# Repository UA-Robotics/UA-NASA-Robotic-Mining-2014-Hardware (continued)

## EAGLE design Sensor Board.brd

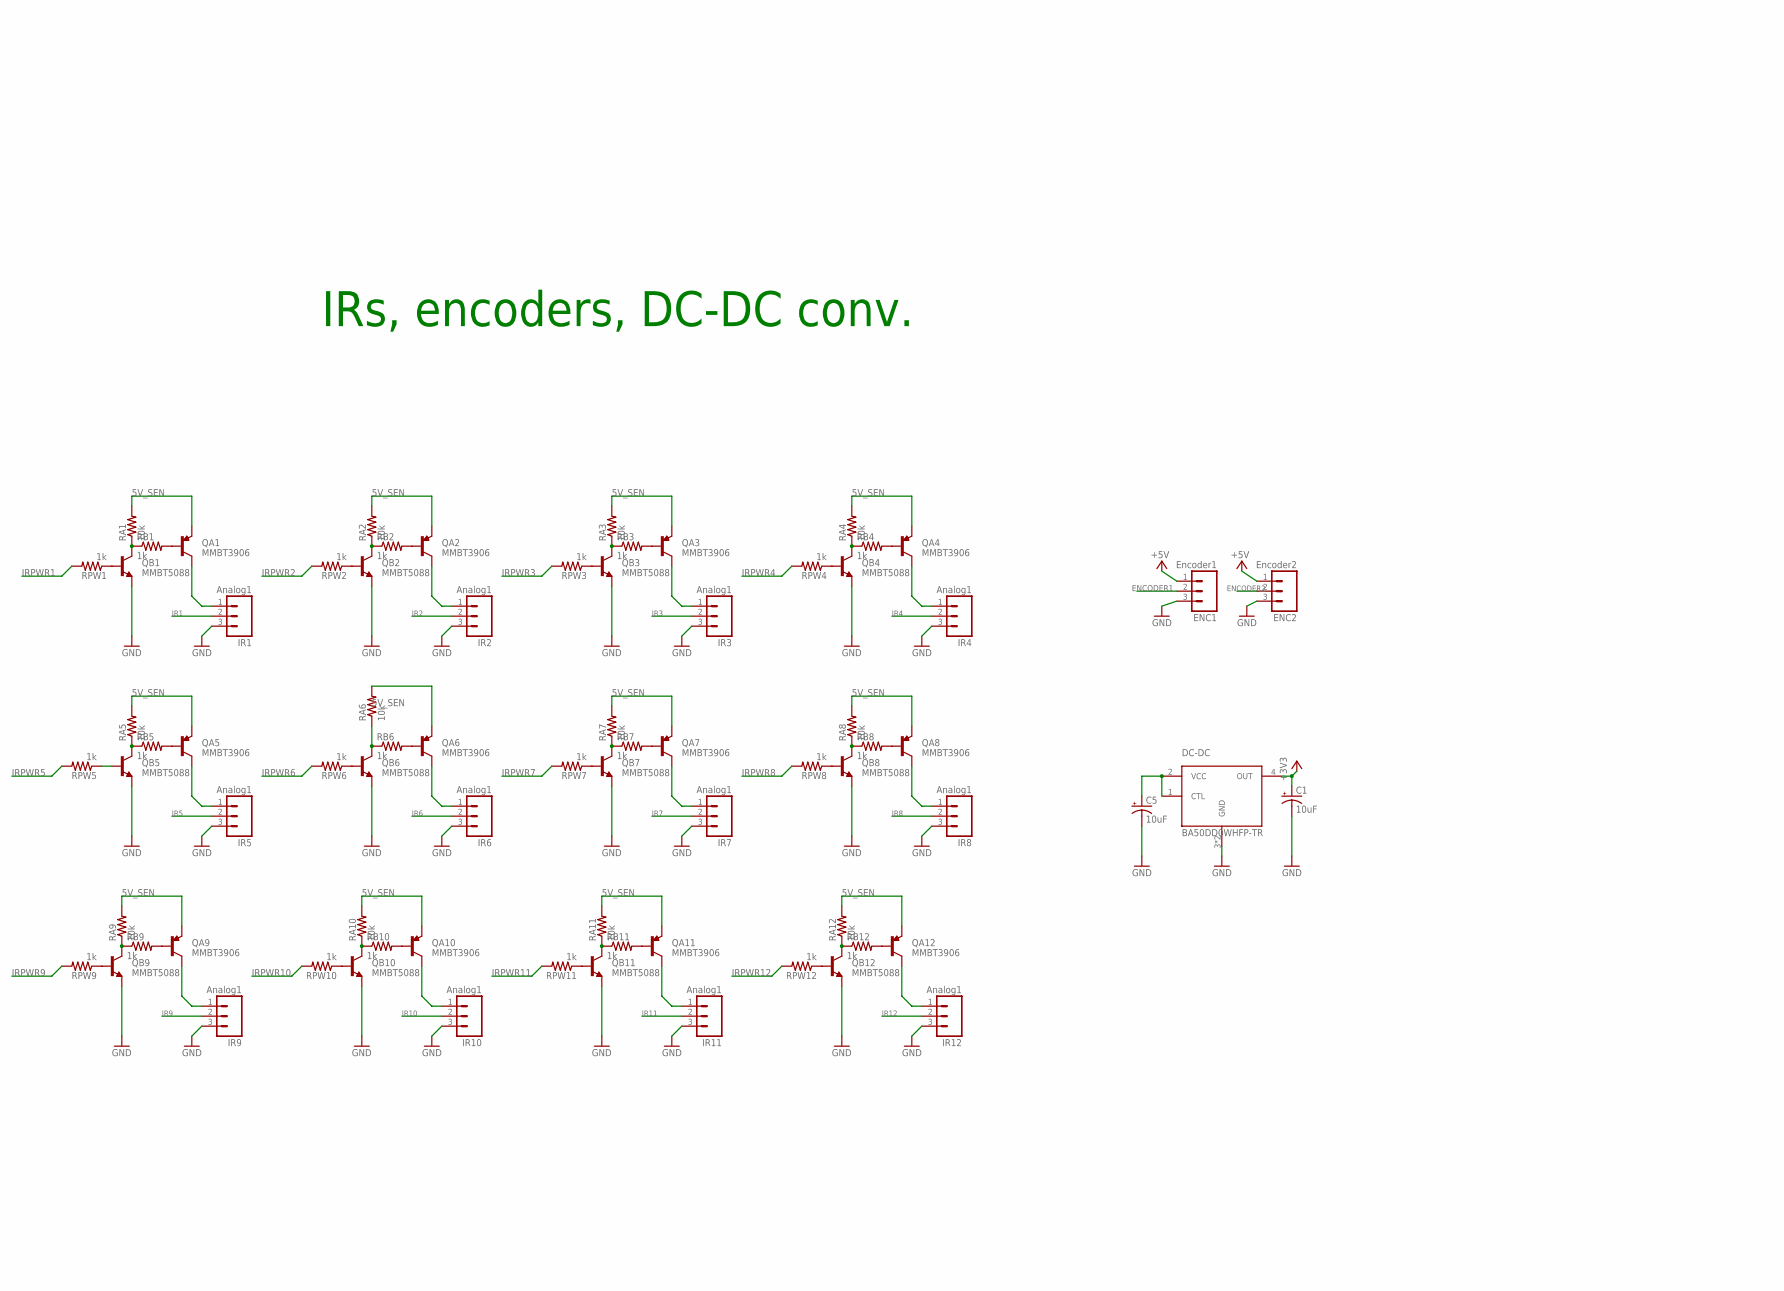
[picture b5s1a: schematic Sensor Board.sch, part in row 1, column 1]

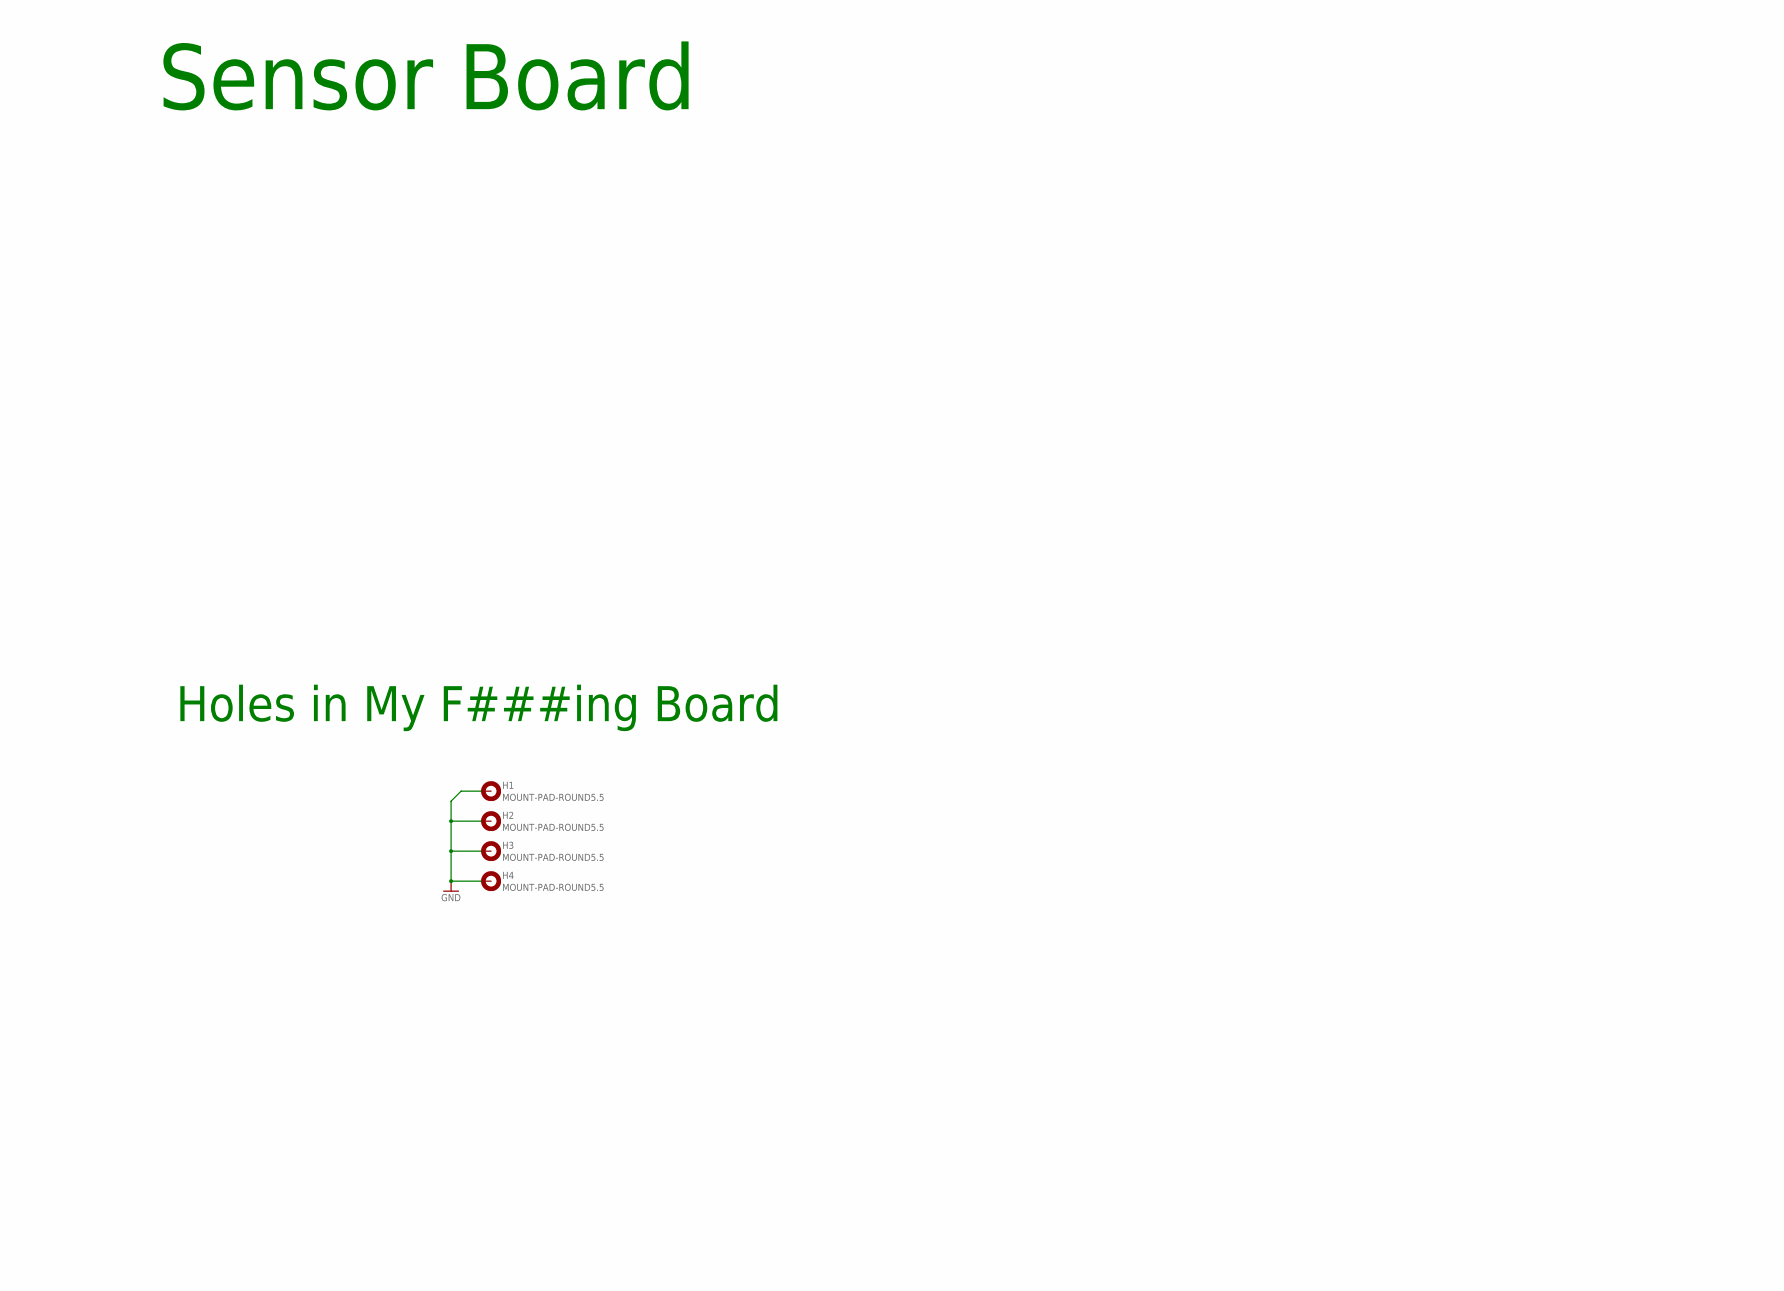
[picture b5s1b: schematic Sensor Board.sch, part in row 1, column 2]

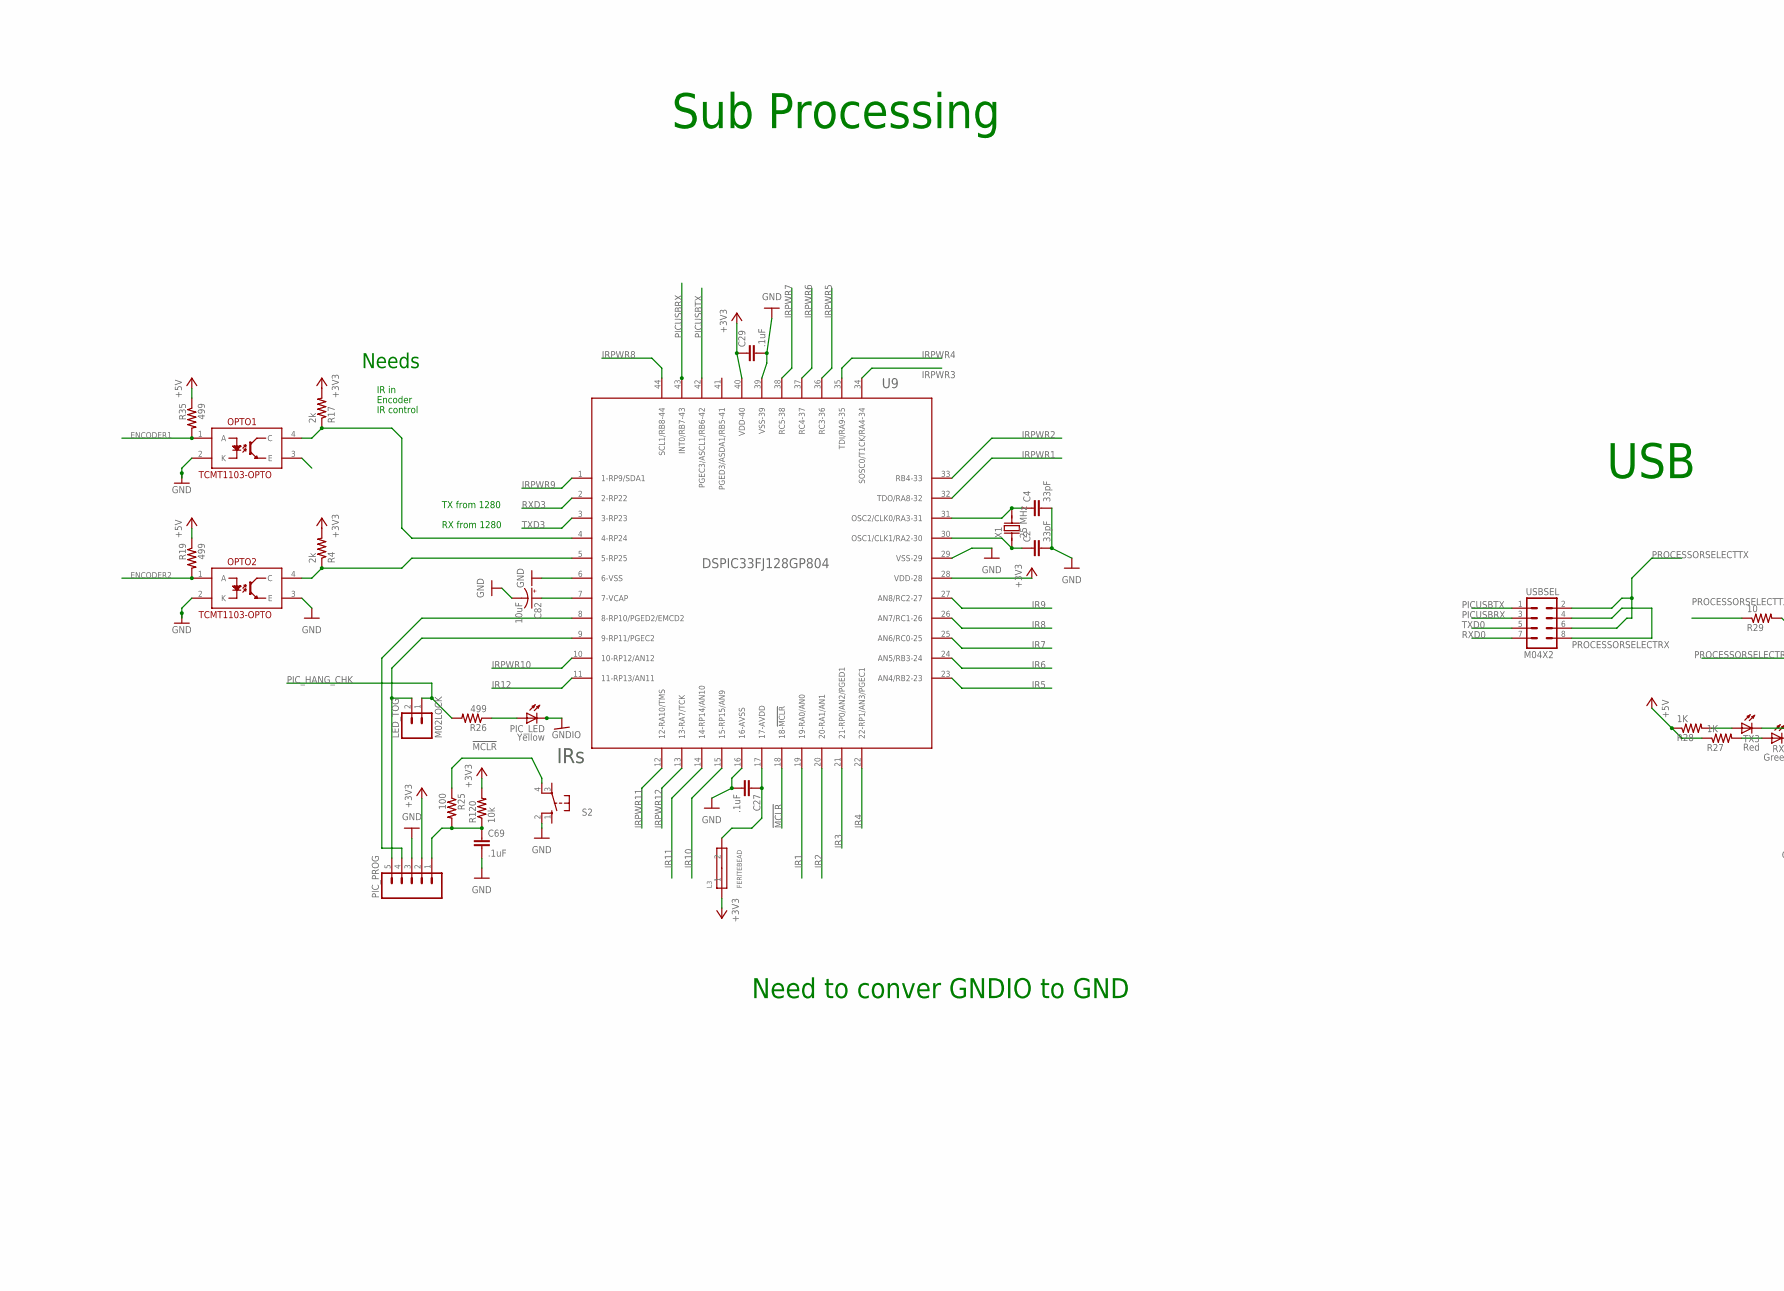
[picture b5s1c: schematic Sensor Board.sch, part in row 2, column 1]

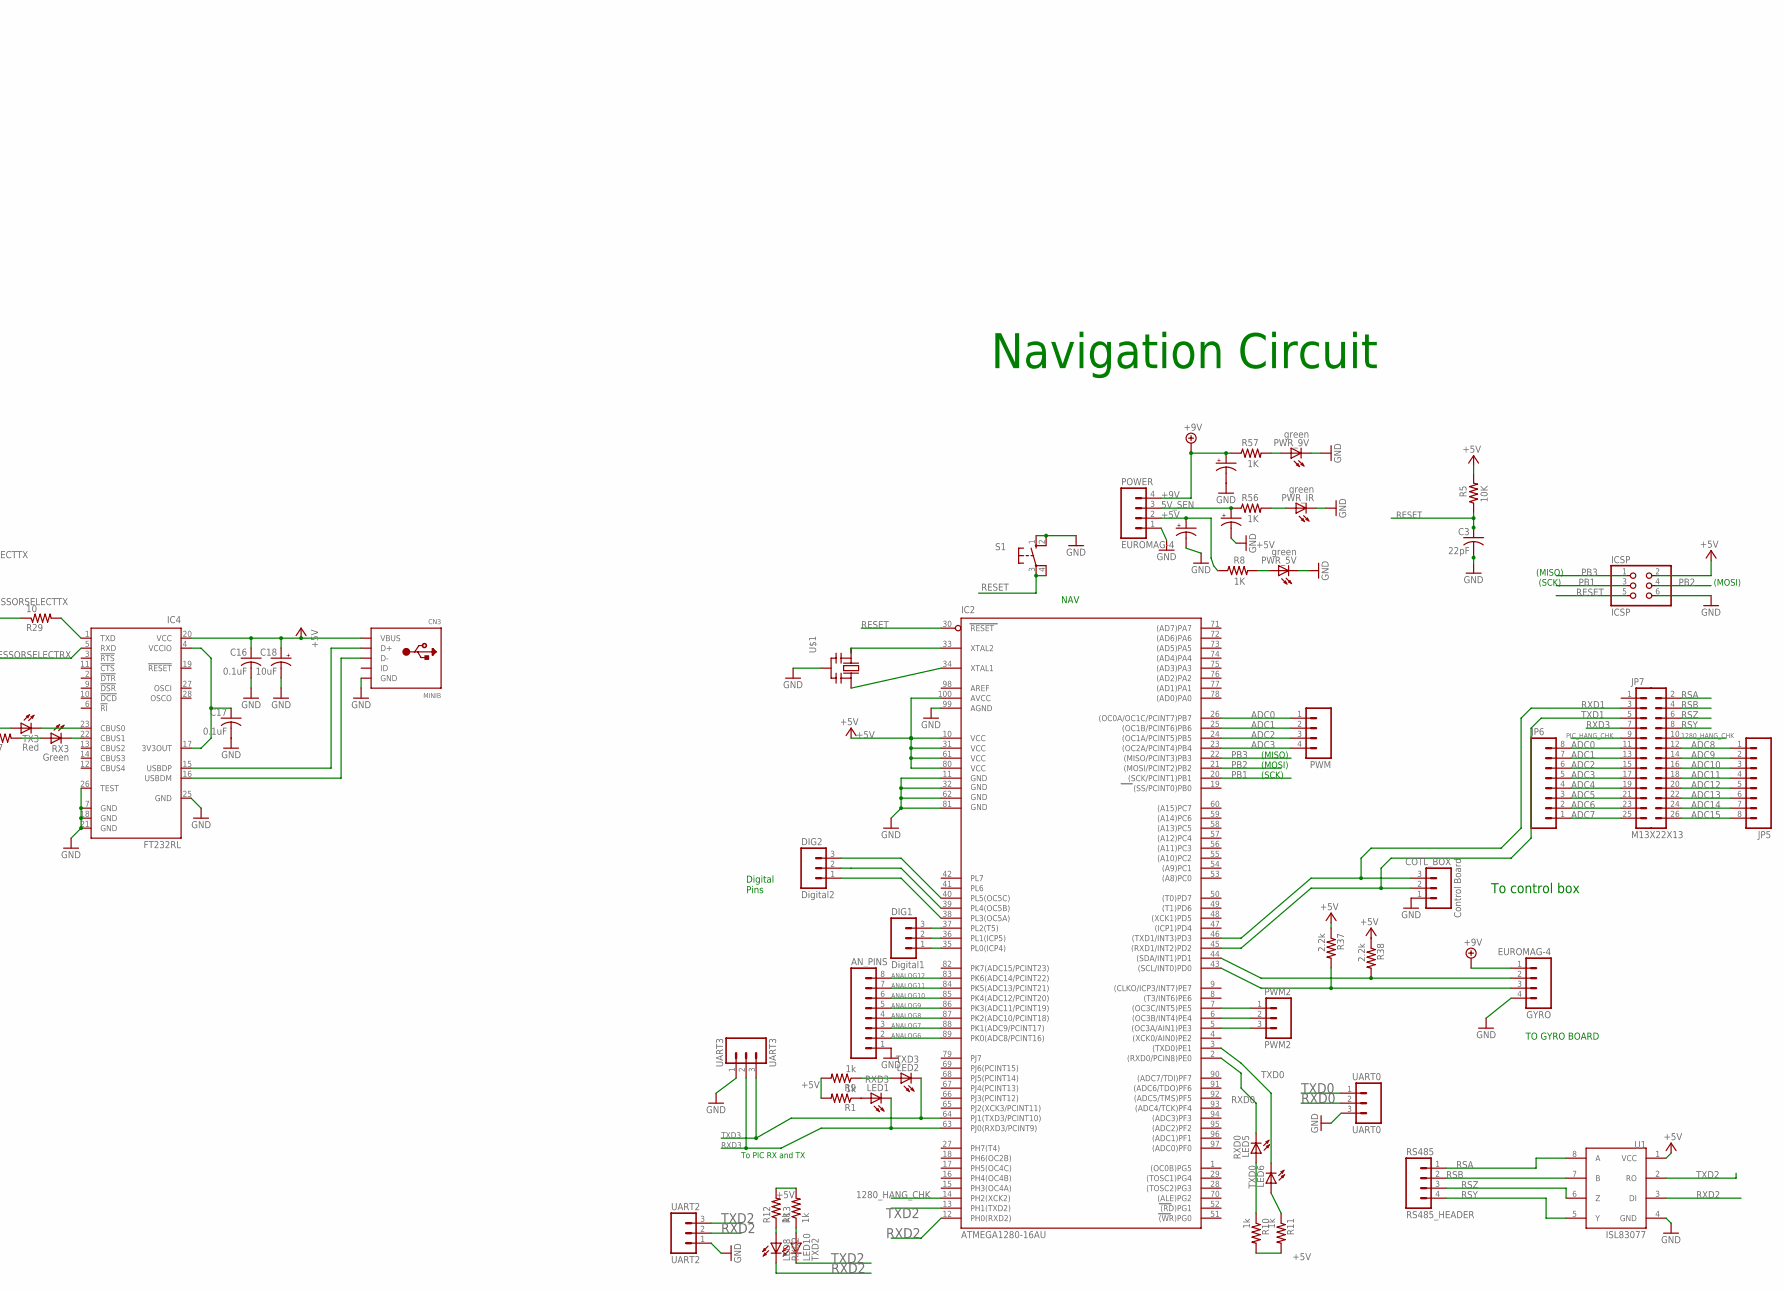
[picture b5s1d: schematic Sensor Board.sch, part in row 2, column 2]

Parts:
AN_PINS: M08LOCK_LONGPADS; 1X08_LOCK_LONGPADS
C1, C5: 10uF; EIA3216
C2, C4: 33pF; 0805
C3: 22pF; C0805K
C16, C17: 0.1uF; C0805K
C18: 10uF; EIA3528-KIT
C27, C29, C69: .1uF; 0805
C82: 10uF; POLC1206
CAN1, CAN2, CAN3: EMVY160ADA101MF55G; 140CLH-1010
CN3: MINIB; USB-MINIB
COTL_BOX: Control Board; MOLEX-1X3_LOCK
DC-DC: BA50DD0WHFP-TR; HRP5
DIG1: Digital1; M3
DIG2: Digital2; M3
ENC1: Encoder1; M3
ENC2: Encoder2; M3
GYRO: EUROMAG-4; M4
H1, H2, H3, H4: MOUNT-PAD-ROUND5.5; 5,5-PAD
IC2: ATMEGA1280-16AU; TQFP100
IC4: FT232RL; SSOP28
ICSP: ICSP; 2X03
IR1, IR2, IR3, IR4, IR5, IR6, IR7, IR8, IR9, IR10, IR11, IR12: Analog1; M3
JP5, JP6: M08LOCK_LONGPADS; 1X08_LOCK_LONGPADS
JP7: M13X22X13; 2X13
L3: FERITEBEAD; 0603
LED1: RXD3; CHIP-LED0805
LED2: TXD3; CHIP-LED0805
LED5: RXD0; CHIP-LED0805
LED6: TXD0; CHIP-LED0805
LED8: RXD2; CHIP-LED0805
LED10: TXD2; CHIP-LED0805
LED_TOG: M02LOCK; 1X02_LOCK
OPTO1, OPTO2: TCMT1103-OPTO; SSOP-4
PIC_LED: Yellow; CHIP-LED0805
PIC_PROG: M05LOCK_LONGPADS; 1X05_LOCK_LONGPADS
POWER: EUROMAG-4; M4
PWM: M04POLAR; MOLEX-1X4
PWM2: PWM2; MOLEX-1X3_LOCK
PWR_5V, PWR_9V: green; CHIPLED_0805
PWR_IR: green; CHIPLED_0805
QA1, QA2, QA3, QA4, QA5, QA6, QA7, QA8, QA9, QA10, QA11, QA12: MMBT3906; SOT23
QB1, QB2, QB3, QB4, QB5, QB6, QB7, QB8, QB9, QB10, QB11, QB12: MMBT5088; SOT23
R1, R9, R10, R11, R12, R13: 1k; R0805
R4, R17: 2k; R0805
R5: 10K; R0805
R8, R27, R28, R56, R57: 1K; R0805
R19, R26, R35: 499; R0805
R25: 100; R0805
R29: 10; R0805
R37, R38: 2.2k; R0805
R120: 10k; R0805
RA1, RA2, RA3, RA4, RA5, RA6, RA7, RA8, RA9, RA10, RA11, RA12: 10k; 0805
RB1, RB2, RB3, RB4, RB5, RB6, RB7, RB8, RB9, RB10, RB11, RB12: 1k; 0805
RPW1, RPW2, RPW3, RPW4, RPW5, RPW6, RPW7, RPW8, RPW9, RPW10, RPW11, RPW12: 1k; 0805
RS485_HEADER: RS485; M4-90
RX3: Green; CHIP-LED0805
S1, S2: 10-XX; B3F-10XX
TX3: Red; CHIP-LED0805
U1: ISL83077; SO08
U9: DSPIC33FJ128GP804; TQFP-44
U$1: CERMOSCILL-AWCSR; AWCSR
UART0: UART0; 1X03
UART2: UART2; 1X03
UART3: UART3; 1X03
USBSEL: M04X2; 2X4
X1: 25 MHz; XRCGB-CYL

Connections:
5V_SEN: CAN2.+, POWER.3, QA1.2 (E), QA2.2 (E), QA3.2 (E), QA4.2 (E), QA5.2 (E), QA6.2 (E), QA7.2 (E), QA8.2 (E), QA9.2 (E), QA10.2 (E), QA11.2 (E), QA12.2 (E), R56.1, RA1.2, RA2.2, RA3.2, RA4.2, RA5.2, RA6.2, RA7.2, RA8.2, RA9.2, RA10.2, RA11.2, RA12.2
1280_HANG_CHK: IC2.14 (PH2(XCK2)), JP7.10
!MCLR: R25.1, S2.4 (P1), U9.18 (18-!MCLR)
+3V3: C1.A (+), C29.1, DC-DC.4 (OUT), L3.1, PIC_PROG.2, R4.2, R17.2, R120.2, U9.28 (VDD-28), U9.40 (VDD-40)
+5V: C5.A (+), C16.1, C18.A (+), CAN3.+, CN3.VBUS, DC-DC.1 (CTL), DC-DC.2 (VCC), ENC1.1, ENC2.1, IC2.10 (VCC), IC2.31 (VCC1), IC2.61 (VCC2), IC2.80 (VCC3), IC2.100 (AVCC), IC4.20 (VCC), ICSP.2, POWER.2, R1.2, R5.2, R8.1, R9.2, R10.2, R11.2, R12.2, R13.2, R19.1, R27.1, R28.1, R35.1, R37.1, R38.1, U1.1 (VCC)
+9V: CAN1.+, GYRO.1, POWER.4, R57.1
ADC0: IC2.26 ((OC0A/OC1C/PCINT7)PB7), JP6.8, JP7.11, PWM.1
ADC1: IC2.25 ((OC1B/PCINT6)PB6), JP6.7, JP7.13, PWM.2
ADC2: IC2.24 ((OC1A/PCINT5)PB5), JP6.6, JP7.15, PWM.3
ADC3: IC2.23 ((OC2A/PCINT4)PB4), JP6.5, JP7.17, PWM.4
ADC4: JP6.4, JP7.19
ADC5: JP6.3, JP7.21
ADC6: JP6.2, JP7.23
ADC7: JP6.1, JP7.25
ADC8: JP5.1, JP7.12
ADC9: JP5.2, JP7.14
ADC10: JP5.3, JP7.16
ADC11: JP5.4, JP7.18
ADC12: JP5.5, JP7.20
ADC13: JP5.6, JP7.22
ADC14: JP5.7, JP7.24
ADC15: JP5.8, JP7.26
ANALOG6: AN_PINS.2, IC2.89 (PK0(ADC8/PCINT16))
ANALOG7: AN_PINS.3, IC2.88 (PK1(ADC9/PCINT17))
ANALOG8: AN_PINS.4, IC2.87 (PK2(ADC10/PCINT18))
ANALOG9: AN_PINS.5, IC2.86 (PK3(ADC11/PCINT19))
ANALOG10: AN_PINS.6, IC2.85 (PK4(ADC12/PCINT20))
ANALOG11: AN_PINS.7, IC2.84 (PK5(ADC13/PCINT21))
ANALOG12: AN_PINS.8, IC2.83 (PK6(ADC14/PCINT22))
ANBNKJDFBNDFKJL: OPTO1.4 (C), R17.1, U9.4 (4-RP24)
ANBNKJDFBNDFKJL1: OPTO2.4 (C), R4.1, U9.5 (5-RP25)
ENCODER1: ENC1.2, OPTO1.1 (A), R35.2
ENCODER2: ENC2.2, OPTO2.1 (A), R19.2
GND: AN_PINS.1, C1.C (-), C2.2, C3.2, C4.2, C5.C (-), C16.2, C17.2, C18.C (-), C27.2, C29.2, C69.2, C82.2 (-), CAN1.-, CAN2.-, CAN3.-, CN3.GND, COTL_BOX.1, DC-DC.3 (GND), DC-DC.G (GND), ENC1.3, ENC2.3, GYRO.4, H1.B5,5, H2.B5,5, H3.B5,5, H4.B5,5, IC2.11 (GND), IC2.32 (GND1), IC2.62 (GND2), IC2.81 (GND3), IC2.99 (AGND), IC4.7 (GND), IC4.18 (GND), IC4.21 (GND), IC4.25 (GND), IC4.26 (TEST), ICSP.6, IR1.3, IR2.3, IR3.3, IR4.3, IR5.3, IR6.3, IR7.3, IR8.3, IR9.3, IR10.3, IR11.3, IR12.3, OPTO1.2 (K), OPTO2.2 (K), OPTO2.3 (E), PIC_PROG.3, POWER.1, PWR_5V.C, PWR_9V.C, PWR_IR.C, QB1.2 (E), QB2.2 (E), QB3.2 (E), QB4.2 (E), QB5.2 (E), QB6.2 (E), QB7.2 (E), QB8.2 (E), QB9.2 (E), QB10.2 (E), QB11.2 (E), QB12.2 (E), S1.1 (S), S1.2 (S1), S2.2 (S1), U1.4 (GND), U9.6 (6-VSS), U9.16 (16-AVSS), U9.29 (VSS-29), U9.39 (VSS-39), U$1.2 (GND), UART0.3, UART2.1, UART3.1
GNDIO: PIC_LED.C
IR1: IR1.2, U9.19 (19-RA0/AN0)
IR2: IR2.2, U9.20 (20-RA1/AN1)
IR3: IR3.2, U9.21 (21-RP0/AN2/PGED1)
IR4: IR4.2, U9.22 (22-RP1/AN3/PGEC1)
IR5: IR5.2, U9.23 (AN4/RB2-23)
IR6: IR6.2, U9.24 (AN5/RB3-24)
IR7: IR7.2, U9.25 (AN6/RC0-25)
IR8: IR8.2, U9.26 (AN7/RC1-26)
IR9: IR9.2, U9.27 (AN8/RC2-27)
IR10: IR10.2, U9.15 (15-RP15/AN9)
IR11: IR11.2, U9.14 (14-RP14/AN10)
IR12: IR12.2, U9.11 (11-RP13/AN11)
IRPWR1: RPW1.2, U9.32 (TDO/RA8-32)
IRPWR2: RPW2.2, U9.33 (RB4-33)
IRPWR3: RPW3.2, U9.34 (SOSC0/T1CK/RA4-34)
IRPWR4: RPW4.2, U9.35 (TDI/RA9-35)
IRPWR5: RPW5.2, U9.36 (RC3-36)
IRPWR6: RPW6.2, U9.37 (RC4-37)
IRPWR7: RPW7.2, U9.38 (RC5-38)
IRPWR8: RPW8.2, U9.44 (SCL1/RB8-44)
IRPWR9: RPW9.2, U9.1 (1-RP9/SDA1)
IRPWR10: RPW10.2, U9.10 (10-RP12/AN12)
IRPWR11: RPW11.2, U9.12 (12-RA10/TMS)
IRPWR12: RPW12.2, U9.13 (13-RA7/TCK)
unnamed: QA2.1 (B), RB2.2
unnamed: QB2.3 (C), RA2.1, RB2.1
unnamed: PWR_5V.A, R8.2
unnamed: QB2.1 (B), RPW2.1
unnamed: QA1.1 (B), RB1.2
unnamed: IC2.34 (XTAL1), U$1.3 (OUT)
unnamed: IC2.33 (XTAL2), U$1.1 (IN)
unnamed: QB1.3 (C), RA1.1, RB1.1
unnamed: QB1.1 (B), RPW1.1
unnamed: IR1.1, QA1.3 (C)
unnamed: PIC_PROG.4, U9.8 (8-RP10/PGED2/EMCD2)
unnamed: LED2.A, R9.1
unnamed: C4.1, U9.31 (OSC2/CLK0/RA3-31), X1.3 (OUT)
unnamed: C2.1, U9.30 (OSC1/CLK1/RA2-30), X1.1 (IN)
unnamed: C69.1, PIC_PROG.1, R25.2, R120.1
unnamed: C82.1 (+), U9.7 (7-VCAP)
unnamed: IR2.1, QA2.3 (C)
unnamed: QA3.1 (B), RB3.2
unnamed: QB3.3 (C), RA3.1, RB3.1
unnamed: LED_TOG.2, PIC_PROG.5, U9.9 (9-RP11/PGEC2)
unnamed: QB3.1 (B), RPW3.1
unnamed: IC2.7 ((OC3C/INT5)PE5), PWM2.1
unnamed: C27.1, L3.2, U9.17 (17-AVDD)
unnamed: IR3.1, QA3.3 (C)
unnamed: QA4.1 (B), RB4.2
unnamed: QB4.3 (C), RA4.1, RB4.1
unnamed: QB4.1 (B), RPW4.1
unnamed: IR4.1, QA4.3 (C)
unnamed: QA5.1 (B), RB5.2
unnamed: IC2.6 ((OC3B/INT4)PE4), PWM2.2
unnamed: LED1.A, R1.1
unnamed: IC2.5 ((OC3A/AIN1)PE3), PWM2.3
unnamed: QB5.3 (C), RA5.1, RB5.1
unnamed: QB5.1 (B), RPW5.1
unnamed: LED10.A, R13.1
unnamed: IR5.1, QA5.3 (C)
unnamed: PWR_IR.A, R56.2
unnamed: LED8.A, R12.1
unnamed: PWR_9V.A, R57.2
unnamed: DIG1.1, IC2.35 (PL0(ICP4))
unnamed: LED6.A, R11.1
unnamed: DIG1.2, IC2.36 (PL1(ICP5))
unnamed: QA6.1 (B), RB6.2
unnamed: DIG1.3, IC2.37 (PL2(T5))
unnamed: DIG2.1, IC2.38 (PL3(OC5A))
unnamed: QB6.3 (C), RA6.1, RB6.1
unnamed: DIG2.2, IC2.39 (PL4(OC5B))
unnamed: DIG2.3, IC2.40 (PL5(OC5C))
unnamed: LED5.A, R10.1
unnamed: QB6.1 (B), RPW6.1
unnamed: IR6.1, QA6.3 (C)
unnamed: QA7.1 (B), RB7.2
unnamed: QB7.3 (C), RA7.1, RB7.1
unnamed: QB7.1 (B), RPW7.1
unnamed: GYRO.2, IC2.44 ((SDA/INT1)PD1), R38.2
unnamed: GYRO.3, IC2.43 ((SCL/INT0)PD0), R37.2
unnamed: IR7.1, QA7.3 (C)
unnamed: QA8.1 (B), RB8.2
unnamed: QB8.3 (C), RA8.1, RB8.1
unnamed: QB8.1 (B), RPW8.1
unnamed: IR8.1, QA8.3 (C)
unnamed: QA9.1 (B), RB9.2
unnamed: QB9.3 (C), RA9.1, RB9.1
unnamed: QB9.1 (B), RPW9.1
unnamed: IR9.1, QA9.3 (C)
unnamed: QA10.1 (B), RB10.2
unnamed: QB10.3 (C), RA10.1, RB10.1
unnamed: QB10.1 (B), RPW10.1
unnamed: CN3.D+, IC4.15 (USBDP)
unnamed: CN3.D-, IC4.16 (USBDM)
unnamed: IC4.23 (CBUS0), TX3.C
unnamed: IC4.22 (CBUS1), RX3.C
unnamed: R27.2, RX3.A
unnamed: R28.2, TX3.A
unnamed: IC4.1 (TXD), R29.2
unnamed: C17.1, IC4.4 (VCCIO), IC4.17 (3V3OUT)
unnamed: IR10.1, QA10.3 (C)
unnamed: QA11.1 (B), RB11.2
unnamed: QB11.3 (C), RA11.1, RB11.1
unnamed: QB11.1 (B), RPW11.1
unnamed: IR11.1, QA11.3 (C)
unnamed: QA12.1 (B), RB12.2
unnamed: QB12.3 (C), RA12.1, RB12.1
unnamed: QB12.1 (B), RPW12.1
unnamed: IR12.1, QA12.3 (C)
unnamed: PIC_LED.A, R26.1
PB1: IC2.20 ((SCK/PCINT1)PB1), ICSP.3
PB2: IC2.21 ((MOSI/PCINT2)PB2), ICSP.4
PB3: IC2.22 ((MISO/PCINT3)PB3), ICSP.1
PICUSBRX: U9.43 (INT0/RB7-43), USBSEL.3
PICUSBTX: U9.42 (PGEC3/ASCL1/RB6-42), USBSEL.1
PIC_HANG_CHK: JP7.9, LED_TOG.1, R26.2
PROCESSORSELECTRX: IC4.5 (RXD), USBSEL.4, USBSEL.8
PROCESSORSELECTTX: R29.1, USBSEL.2, USBSEL.6
RESET: C3.1, IC2.30 (RESET), ICSP.5, R5.1, S1.3, S1.4 (P1)
RSA: JP7.2, RS485_HEADER.1, U1.8 (A)
RSB: JP7.4, RS485_HEADER.2, U1.7 (B)
RSY: JP7.8, RS485_HEADER.4, U1.5 (Y)
RSZ: JP7.6, RS485_HEADER.3, U1.6 (Z)
RXD0: IC2.2 ((RXD0/PCIN8)PE0), LED5.C, UART0.2, USBSEL.7
RXD1: COTL_BOX.3, IC2.46 ((TXD1/INT3)PD3), JP7.3
RXD2: IC2.12 (PH0(RXD2)), LED8.C, U1.3 (DI), UART2.2
RXD3: IC2.63 (PJ0(RXD3/PCINT9)), JP7.7, LED1.C, U9.2 (2-RP22), UART3.2
TXD0: IC2.3 ((TXD0)PE1), LED6.C, UART0.1, USBSEL.5
TXD1: COTL_BOX.2, IC2.45 ((RXD1/INT2)PD2), JP7.5
TXD2: IC2.13 (PH1(TXD2)), LED10.C, U1.2 (RO), UART2.3
TXD3: IC2.64 (PJ1(TXD3/PCINT10)), LED2.C, U9.3 (3-RP23), UART3.3

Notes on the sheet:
(SCK)
(MISO)
(MOSI)
Sensor Board
Digital Pins
Sub Processing
NAV
IR in
Encoder
IR control
To control box
IRs
USB
Navigation Circuit
Holes in My F###ing Board
To PIC RX and TX
Needs
TO GYRO BOARD
IRs, encoders, DC-DC conv.
Need to conver GNDIO to GND
TX from 1280
RX from 1280

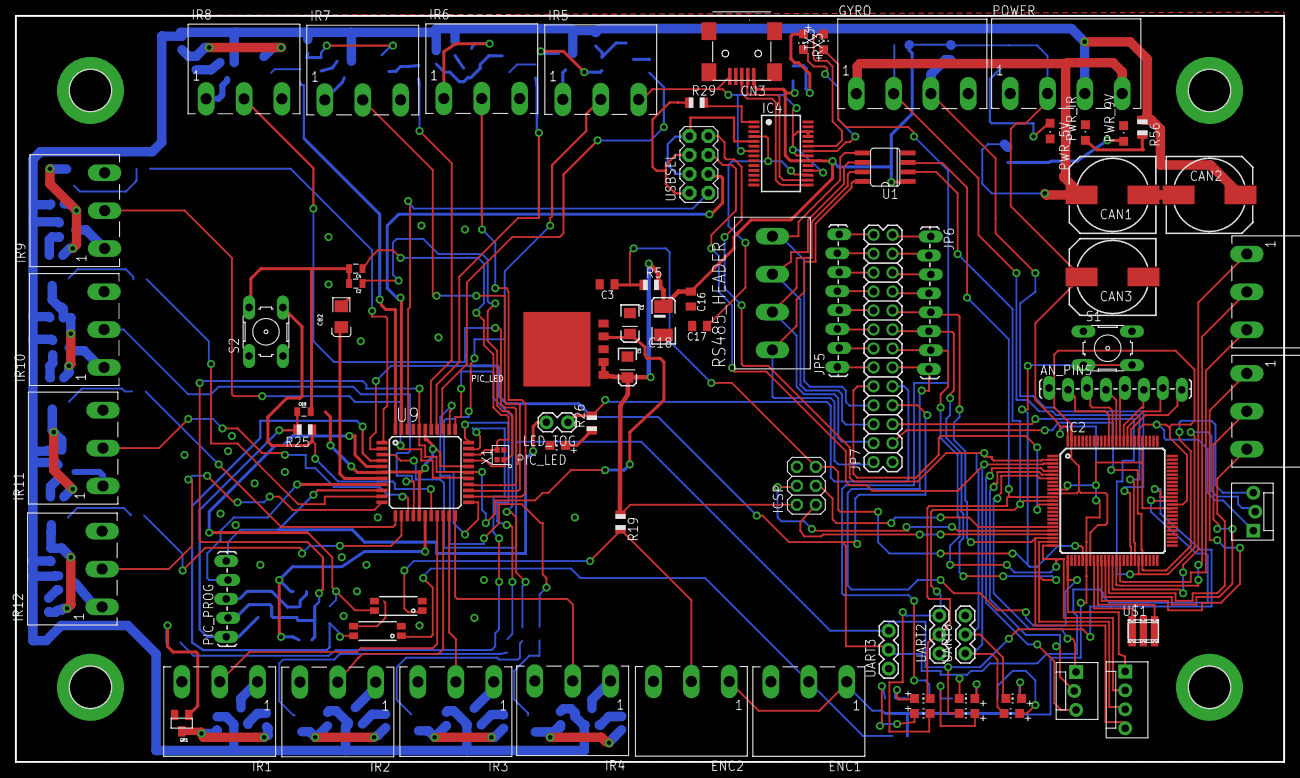
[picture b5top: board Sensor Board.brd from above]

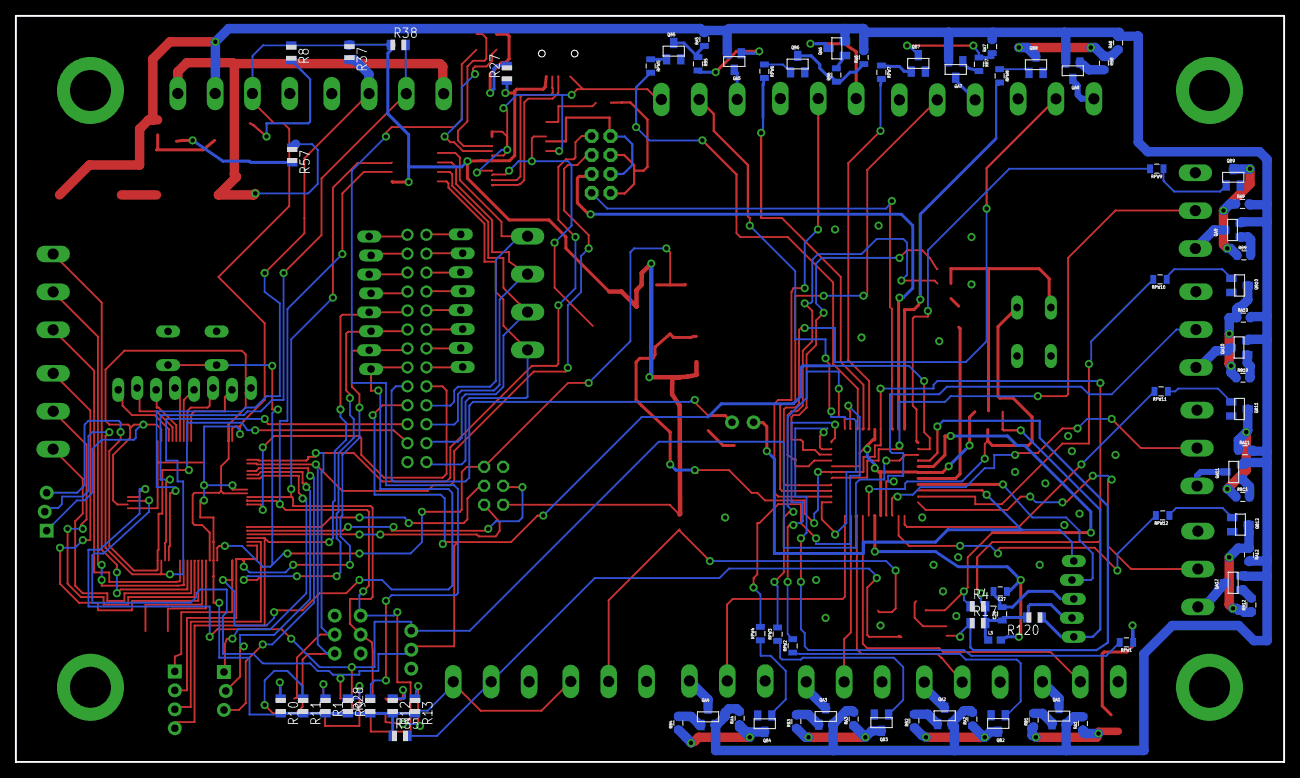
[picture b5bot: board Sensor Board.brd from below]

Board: 2 copper layers, 170.0 x 100.0 mm, 159 parts (78 on the bottom side), 165 nets.

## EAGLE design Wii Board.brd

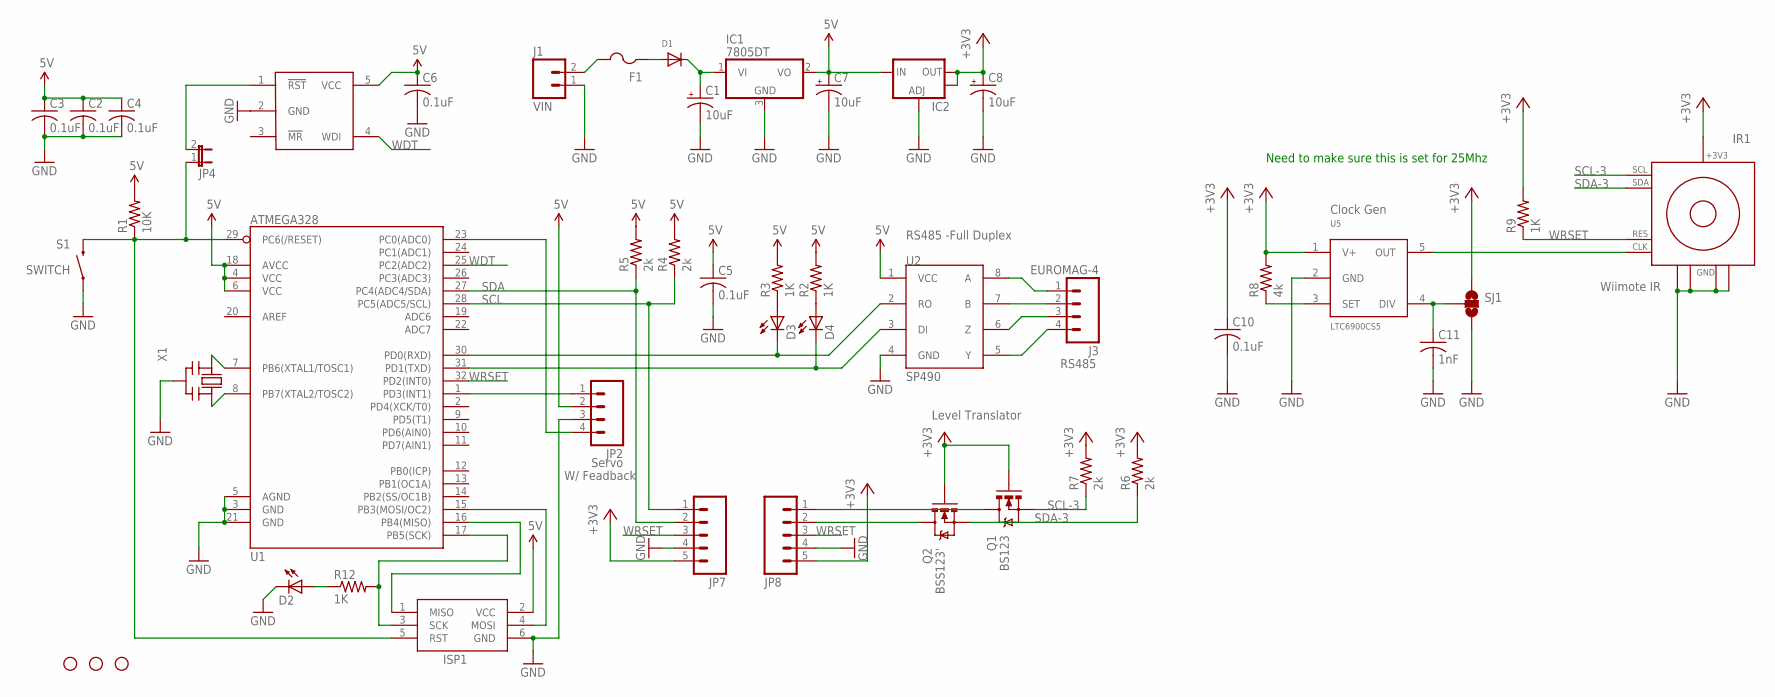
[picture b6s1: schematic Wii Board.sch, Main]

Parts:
C1: 10uF; CT6032
C2, C3, C4, C5, C6, C10: 0.1uF; C0805
C7: 10uF; CT3216
C8: 10uF; CT3528
C11: 1nF; C0805
D1: DIODESMA; SMADIODE
D2, D3, D4: LEDCHIPLED_0805; CHIPLED_0805
F1: PTCFUSE-1206; R1206
IC1: 7805DT; TO252
IC2: V_REG_LM1117SOT223; SOT223
IR1: Wiimote IR; WII_IR_SENSOR
ISP1: AVRISP-6; AVRISP
J1: VIN; M2
J3: EUROMAG-4; M4
JP1, JP3, JP5: STAND-OFF
JP2: M04LOCK; 1X04_LOCK
JP4: JUMPER-2SMD-NO; SJ_2S-NO
JP7, JP8: M05LOCK_LONGPADS; 1X05_LOCK_LONGPADS
Q1: BS123; SOT23
Q2: BSS123'; SOT23
R1: 10K; M0805
R2, R3, R9, R12: 1K; M0805
R4, R5, R6, R7: 2k; M0805
R8: 4k; M0805
S1: SWITCH; TACTILE-PTH
SJ1: SOLDERJUMPER_2WAYS; SJ_3
U1: ATMEGA328; TQFP32-08
U2: SP490; SO08
U3: MAX823; SOT23-5L
U5: LTC6900CS5; TSOT-23-5
X1: CERMOSCILL-AWCSR; AWCSR

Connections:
5V: C2.1, C3.1, C4.1, C5.1, C6.1, C7.+, IC1.2 (VO), IC2.3 (IN), ISP1.2 (VCC), JP2.2, R1.2, R2.2, R3.2, R4.2, R5.2, U1.4 (VCC), U1.6 (VCC), U1.18 (AVCC), U2.1 (VCC), U3.5 (VCC)
+3V3: C8.+, C10.1, IC2.2 (OUT), IC2.4 (OUT), IR1.1_+3V3 (+3V3), JP7.5, JP8.5, Q1.1 (G), Q2.1 (G), R6.2, R7.2, R8.2, R9.2, SJ1.1, U5.1 (V+)
C5: ISP1.4 (MOSI), U1.15 (PB3(MOSI/OC2))
GND: C1.-, C2.2, C3.2, C4.2, C5.2, C6.2, C7.-, C8.-, C10.2, C11.2, D2.C, IC1.3 (GND), IC2.1 (ADJ), IR1.2_GND@1 (GND), IR1.3_GND@2 (GND), IR1.GND@3 (GND), IR1.GND@4 (GND), ISP1.6 (GND), J1.1, JP2.3, JP7.4, JP8.4, S1.1, SJ1.3, U1.3 (GND), U1.5 (AGND), U1.21 (GND), U2.4 (GND), U3.2 (GND), U5.2 (GND), X1.2 (GND)
unnamed: D3.C, U1.30 (PD0(RXD)), U2.2 (RO)
unnamed: F1.2, J1.2
unnamed: D4.C, U1.31 (PD1(TXD)), U2.3 (DI)
unnamed: ISP1.5 (RST), JP4.1, R1.1, S1.3 (2), U1.29 (PC6(/RESET))
unnamed: U1.8 (PB7(XTAL2/TOSC2)), X1.3 (OUT)
unnamed: J3.1, U2.8 (A)
unnamed: ISP1.1 (MISO), U1.16 (PB4(MISO))
unnamed: D1.A, F1.1
unnamed: U1.7 (PB6(XTAL1/TOSC1)), X1.1 (IN)
unnamed: D2.A, R12.1
unnamed: J3.2, U2.7 (B)
unnamed: J3.3, U2.6 (Z)
unnamed: C1.+, D1.C, IC1.1 (VI)
unnamed: D4.A, R2.1
unnamed: J3.4, U2.5 (Y)
unnamed: D3.A, R3.1
unnamed: R8.1, U5.3 (SET)
unnamed: JP2.1, U1.1 (PD3(INT1))
unnamed: C11.1, SJ1.2, U5.4 (DIV)
unnamed: IR1.7_CLK (CLK), U5.5 (OUT)
unnamed: JP4.2, U3.1 (!RST)
unnamed: JP2.4, U1.23 (PC0(ADC0))
unnamed: JP8.1, Q1.3 (D)
unnamed: JP8.2, Q2.3 (D)
SCL: JP7.1, R4.1, U1.28 (PC5(ADC5/SCL))
SCL-3: IR1.5_SCL (SCL), Q1.2 (S), R7.1
SCLK: ISP1.3 (SCK), R12.2, U1.17 (PB5(SCK))
SDA: JP7.2, R5.1, U1.27 (PC4(ADC4/SDA))
SDA-3: IR1.6_SDA (SDA), Q2.2 (S), R6.1
WDT: U1.25 (PC2(ADC2)), U3.4 (WDI)
WRSET: IR1.8_RESET (RES), JP7.3, JP8.3, R9.1, U1.32 (PD2(INT0))

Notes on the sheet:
Need to make sure this is set for 25Mhz
Servo
RS485
Clock Gen
Level Translator
RS485 -Full Duplex
W/ Feadback

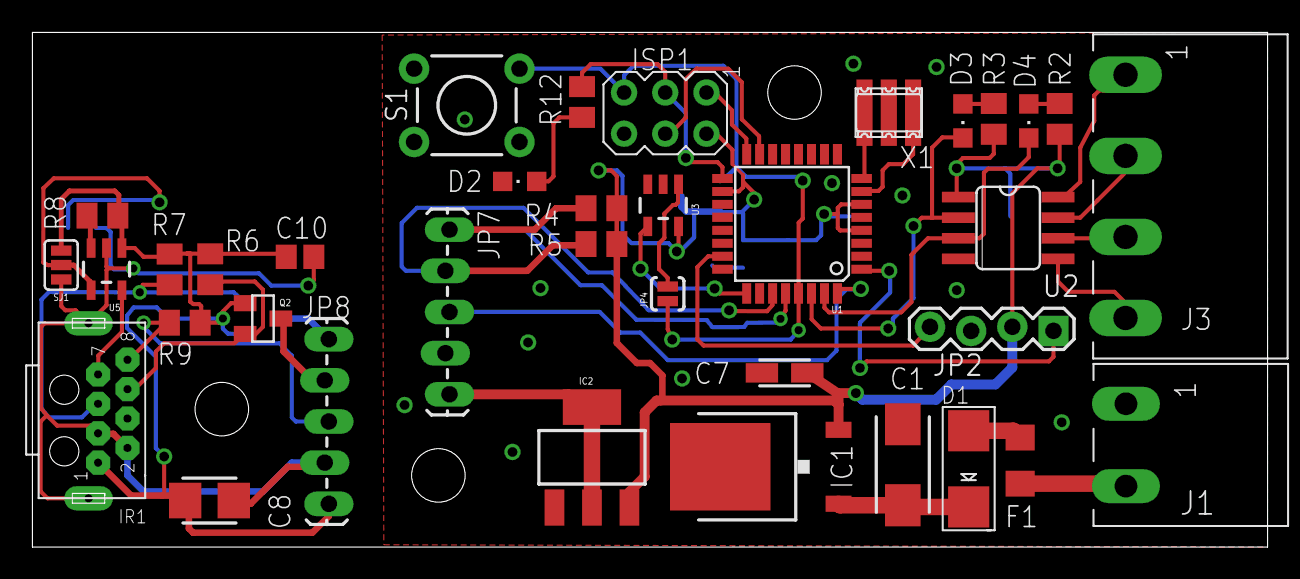
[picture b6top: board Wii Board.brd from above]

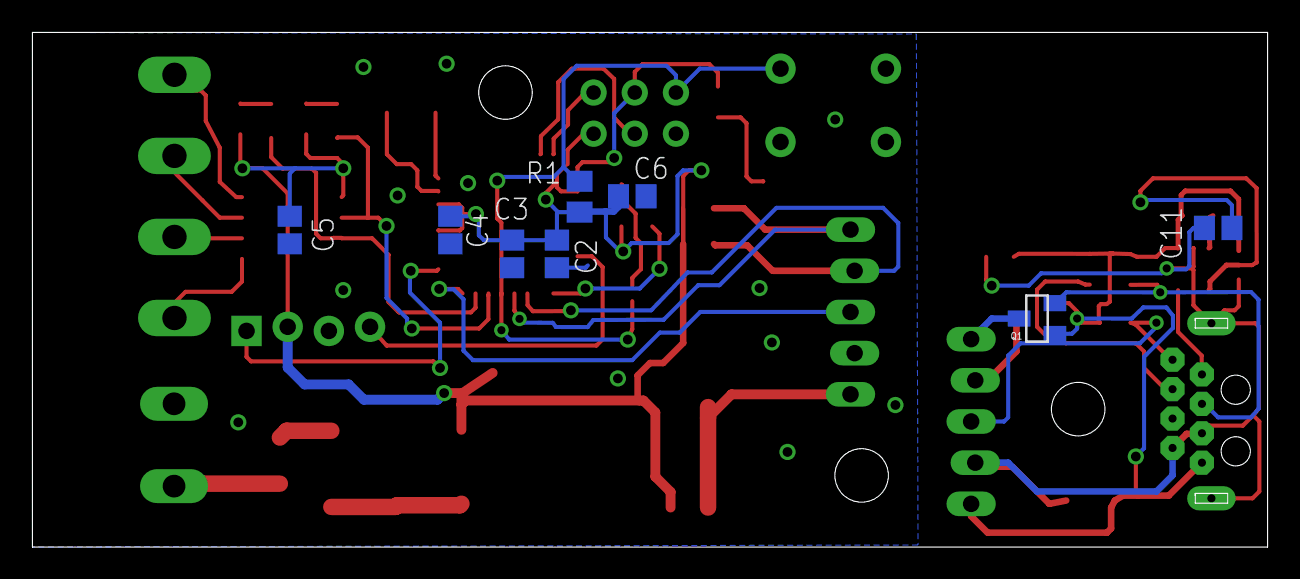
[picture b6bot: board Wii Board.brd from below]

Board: 2 copper layers, 76.2 x 31.8 mm, 47 parts (8 on the bottom side), 35 nets.
